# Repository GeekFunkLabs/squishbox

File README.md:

# SquishBox

- [Official Documentation](https://geekfunklabs.github.io/squishbox)
- [Source Repository](https://github.com/GeekFunkLabs/squishbox)

The SquishBox is a compact add-on board and enclosure for Raspberry Pi
(primarily Pi 3B+ and Pi 4) that combines:

- high-quality stereo DAC with 1/4" outputs
- MIDI in/out via TRS minijacks
- 16x2 character LCD
- pushbutton rotary encoder
- breakout GPIO for extra controls, LEDs, and peripherals

This creates a portable embedded platform for audio projects such as synths,
sound modules, pedalboard utilities, sequencers, and music players.

The software package includes ready-to-run applications plus a simple Python API
for building your own.

## Building/Obtaining

This repository includes schematics, PCB fabrication files, BOMs, and enclosure
models for users who want to build their own hardware.

Kits and pre-built units are also available from the Geek Funk Labs
[store](https://geekfunklabs.com/store).

## Installing

The SquishBox software is targeted for a Pi 3B+/4 running Raspberry Pi OS
(64-bit, based on Debian 13 "Trixie") or newer.
Other platforms may work but are not officially tested.

Before installing (even on a fresh system) it's advisable to first run
`sudo apt update && sudo apt upgrade` to update your audio stack.

To run the install script, log in as a regular user and enter:

```bash
bash <(curl -sL geekfunklabs.com/squishbox)
```

Answer the prompts, wait for install to complete,
and reboot the Pi to activate the LCD/button interface.

## Using the SquishBox

On first boot, the SquishBox starts a launcher that lets the user choose
an app to run or modify system settings.
Selections can be made by turning the rotary encoder.
Tapping the rotary encoder confirms a choice.
Pressing and holding the encoder will cancel or return to the previous
screen in most situations.
To safely shut down the SquishBox before disconnecting power,
use the "Shutdown" option in the "Exit" menu.

## Writing SquishBox Apps

The squishbox python package provides access to the LCD,
controls (buttons/encoders), outputs,
and a set of menu-driven interaction helpers.
Here is a simple example app:

```python
import squishbox

sb = squishbox.SquishBox()
card = "hw:sndrpihifiberry"

sb.lcd.clear()
sb.lcd.write("Audio Test", row=0)
while True:
    i, option = sb.menu_choose(["Noise", "Sine", "Exit"], row=1)
    if option == "Noise":
        sb.shell_cmd(f"speaker-test -l2 -c2 -D{card}")
    elif option == "Sine":
        sb.shell_cmd(f"speaker-test -l2 -c2 -tsine -D{card}")
    elif option == "Exit":
        break
```

## Support and Feature Requests

The SquishBox is under active development, and feature requests are
welcome. 

Please post requests/questions to Discussions on GitHub,
and open issues or pull requests for bugs.

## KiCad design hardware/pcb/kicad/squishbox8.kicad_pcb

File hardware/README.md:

# SquishBox Hardware

This directory contains the design and fabrication files for the SquishBox PCB and enclosure. These files are sufficient to fabricate the PCB, source components, and 3D-print a complete enclosure.

Editable design files are also provided to support modification and customization. If anything is missing or unclear, please open a GitHub issue or contact [albedozero@geekfunklabs.com](mailto:albedozero@geekfunklabs.com).

## Directory Structure

```shell
hardware/
  pcb/
    fabrication/    # Gerbers, drill files, pick-and-place, BOM
    kicad/          # KiCad source design files
  enclosure/
    print/          # STL and 3MF files for slicing
    freecad/        # FreeCAD source design files
    step/           # STEP files for other CAD software
```

## PCB Details

The fabrication files include only surface-mount components for automated assembly. Through-hole components are intended to be sourced separately and soldered by hand.

Insert through-hole components from the side matching the silkscreen outlines.

Install the LCD module last, as it blocks access to several solder points.

### P1 Header

Unused pins from the Raspberry Pi GPIO header are broken out to P1 for attaching additional buttons/outputs. Pins 4 and 7 are connected to ground through 1k resistors, to allow connecting LEDs without additional components.

| P1 pin | pad shape | function        |
|--------|-----------|-----------------|
|  1     | diamond   | 5V              |
|  2     | diamond   | 3.3V            |
|  3     | circle    | GPIO4           |
|  4     | notched   | 1k → GND        |
|  5     | circle    | GPIO2 (I2C SDA) |
|  6     | circle    | GPIO3 (I2C SCL) |
|  7     | notched   | 1k → GND        |
|  8     | circle    | GPIO23          |
|  9     | circle    | GPIO24          |
|  10    | circle    | GPIO10          |
|  11    | circle    | GPIO25          |
|  12    | circle    | GPIO9           |
|  13    | circle    | GPIO11          |
|  14    | square    | GND             |

## Case Details

All parts are designed to be printed flat-side down without supports.

* PLA is sufficient, other materials may be used for desired traits
* Infill amount is not critical due to the small interior volume
* Use at least 2–3 wall layers for adequate strength

Three enclosure variants are provided:

* **basic** — Fits Raspberry Pi 3 Model B+ / Raspberry Pi 4 Model B. A Raspberry Pi 5 can fit, but not with the standard fan installed.
* **deluxe** — Fits Pi 3/4 and includes mounting points for two momentary footswitches and two LEDs, which can be connected to the P1 header on the SquishBox PCB.
* **mini** — Fits Raspberry Pi Model A+, with an enlarged cutout to accommodate wide USB cables or adapters.

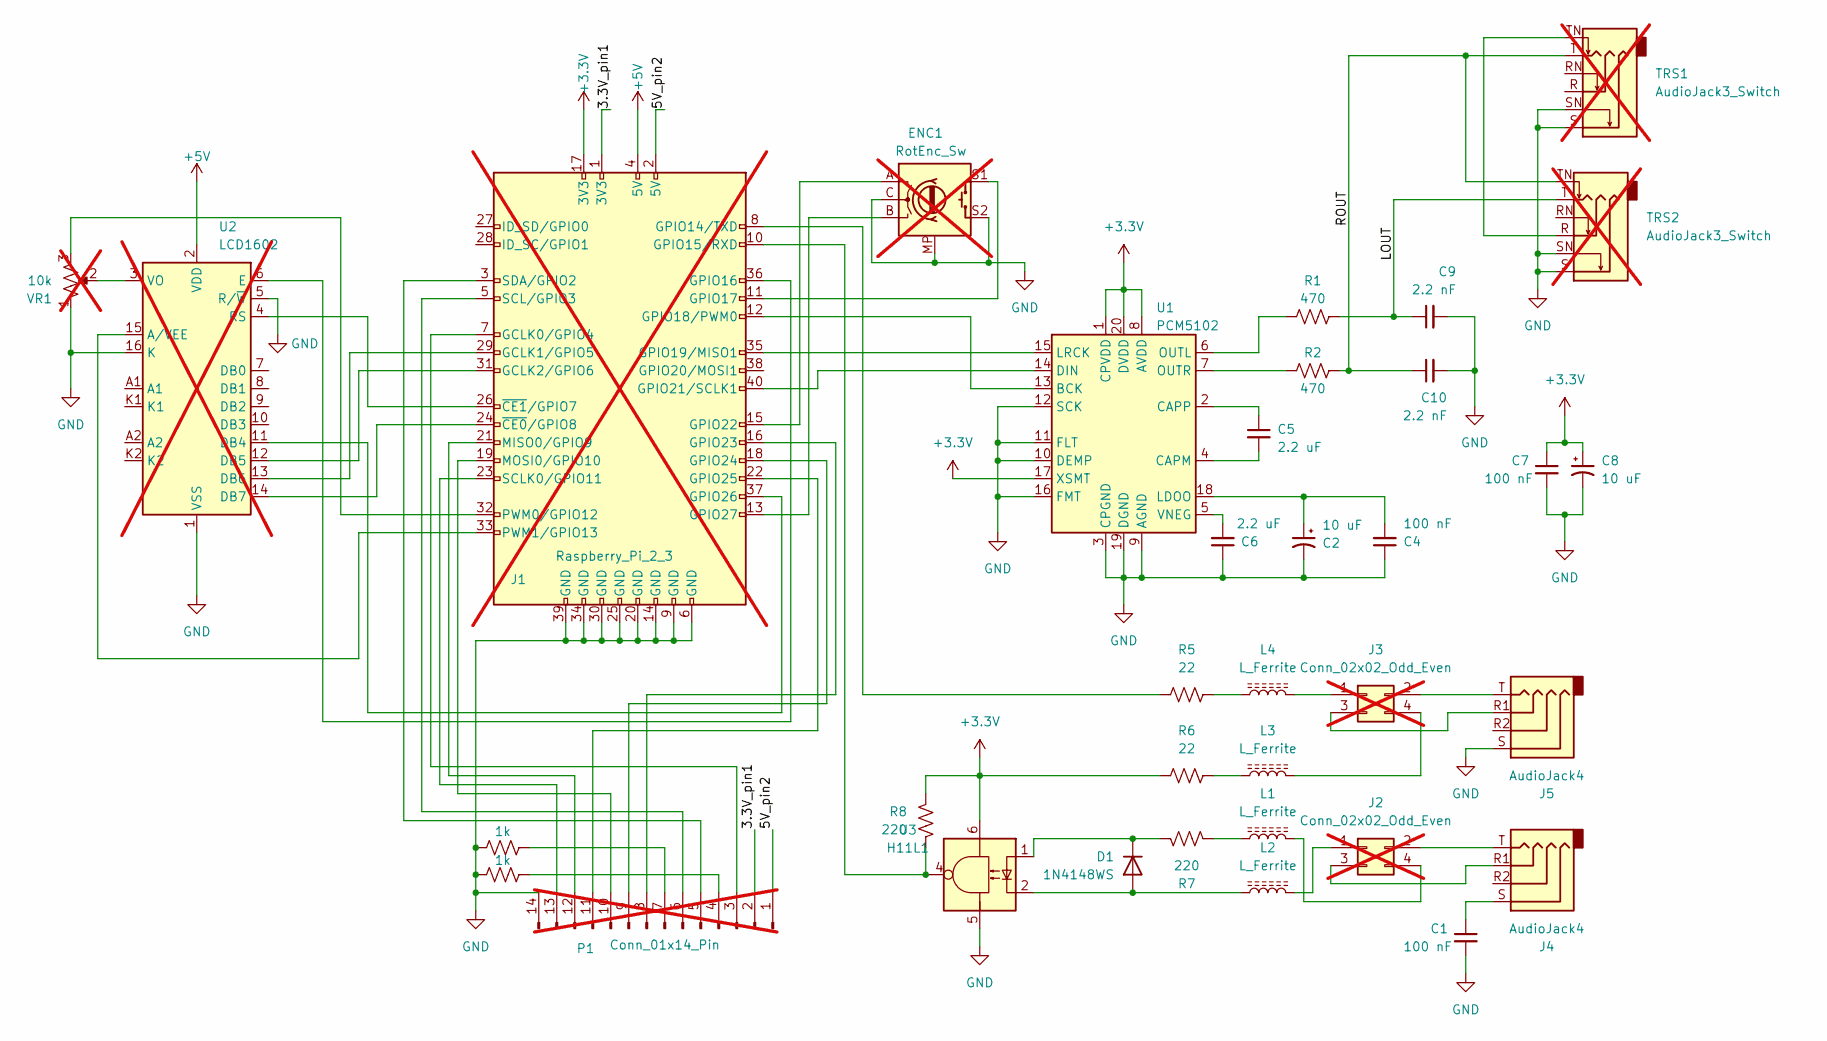
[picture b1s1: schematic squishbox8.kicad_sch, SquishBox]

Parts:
C1, C4, C7: 100 nF; C_0805_2012Metric; MPN 0805F104M500NT; LCSC C28378
C2, C8: 10 uF; C_0805_2012Metric; MPN 0805B106K100NT; LCSC C90544
C5, C6: 2.2 uF; C_0805_2012Metric; MPN 0805B225K250NT; LCSC C74690
C9, C10: 2.2 nF; C_0805_2012Metric; MPN 0805B222K101NT; LCSC C49956
D1: 1N4148WS; D_SOD-323; MPN 1N4148WS; LCSC C2128
ENC1: RotEnc_Sw; RotaryEncoder_Alps_EC11E-Switch_Vertical_H20mm; not fitted
J1: Raspberry_Pi_2_3; PinSocket_2x20_P2.54mm_Vertical; not fitted
J2, J3: Conn_02x02_Odd_Even; PinHeader_2x02_P2.54mm_Vertical; not fitted
J4, J5: AudioJack4; Jack_3.5mm_KoreanHropartsElec_PJ-320D-4A_Horizontal; MPN PJ-320D; LCSC C431535
L1, L2, L3, L4: L_Ferrite; L_0603_1608Metric; MPN GZ1608D601TF; LCSC C1002
P1: Conn_01x14_Pin; PinHeader_1x14_P2.54mm_Vertical; not fitted
R1, R2: 470; R_0805_2012Metric; MPN RS-05K471JT; LCSC C119076
R3, R4: 1k; R_0805_2012Metric; MPN ARG05FTC1001; LCSC C218388
R5, R6: 22; R_2010_5025Metric; MPN FRC2010J220TS; LCSC C3000647
R7, R8: 220; R_1206_3216Metric; MPN 1206W4J0221T5E; LCSC C25363
TRS1, TRS2: AudioJack3_Switch; Jack_6.35mm_Neutrik_NMJ6HFD4_Horizontal; not fitted
U1: PCM5102; TSSOP-20_4.4x6.5mm_P0.65mm; MPN PCM5102APWR; LCSC C107671
U2: LCD1602; PinSocket_1x16_P2.54mm_Vertical; not fitted
U3: H11L1; SMDIP-6_W9.53mm; MPN H11L1S(TA); LCSC C78589
VR1: 10k; Potentiometer_Piher_PT-6-V_Vertical; not fitted

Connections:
+3.3V: C7.1, C8.1, J1.17 (3V3), R6.1, R8.1, U1.1 (CPVDD), U1.8 (AVDD), U1.17 (XSMT), U1.20 (DVDD), U3.6
+5V: J1.4 (5V), U2.2 (VDD)
/3.3V_pin1: J1.1 (3V3), P1.2
/5V_pin2: J1.2 (5V), P1.1
/LOUT: C9.1, R1.2, TRS2.T
/ROUT: C10.1, R2.2, TRS1.T, TRS2.TN
GND: C1.2, C2.2, C4.1, C6.1, C7.2, C8.2, C9.2, C10.2, ENC1.C, ENC1.MP, ENC1.S2, J1.6 (GND), J1.9 (GND), J1.14 (GND), J1.20 (GND), J1.25 (GND), J1.30 (GND), J1.34 (GND), J1.39 (GND), J5.S, P1.14, R3.2, R4.2, TRS1.S, TRS1.SN, TRS2.S, TRS2.SN, U1.3 (CPGND), U1.9 (AGND), U1.10 (DEMP), U1.11 (FLT), U1.12 (SCK), U1.16 (FMT), U1.19 (DGND), U2.1 (VSS), U2.5 (R/~W), U2.16 (K), U3.5, VR1.1
unnamed: C1.1, J4.S
unnamed: D1.2 (A), L2.1, U3.2
unnamed: D1.1 (K), R7.1, U3.1
unnamed: J1.7 (GCLK0/GPIO4), P1.3
unnamed: J1.29 (GCLK1/GPIO5), U2.13 (DB6)
unnamed: J1.31 (GCLK2/GPIO6), U2.12 (DB5)
unnamed: J1.8 (GPIO14/TXD), R5.1
unnamed: J1.10 (GPIO15/RXD), R8.2, U3.4
unnamed: J1.36 (GPIO16), U2.6 (E)
unnamed: ENC1.S1, J1.11 (GPIO17)
unnamed: J1.12 (GPIO18/PWM0), U1.13 (BCK)
unnamed: J1.35 (GPIO19/MISO1), U1.15 (LRCK)
unnamed: J1.40 (GPIO21/SCLK1), U1.14 (DIN)
unnamed: ENC1.A, J1.15 (GPIO22)
unnamed: J1.16 (GPIO23), P1.8
unnamed: J1.18 (GPIO24), P1.9
unnamed: J1.22 (GPIO25), P1.11
unnamed: J1.37 (GPIO26), U2.11 (DB4)
unnamed: ENC1.B, J1.13 (GPIO27)
unnamed: J1.21 (MISO0/GPIO9), P1.12
unnamed: J1.19 (MOSI0/GPIO10), P1.10
unnamed: J1.32 (PWM0/GPIO12), VR1.3
unnamed: J1.33 (PWM1/GPIO13), U2.15 (A/VEE)
unnamed: J1.23 (SCLK0/GPIO11), P1.13
unnamed: J1.5 (SCL/GPIO3), P1.6
unnamed: J1.3 (SDA/GPIO2), P1.5
unnamed: J1.24 (~CE0/GPIO8), U2.14 (DB7)
unnamed: J1.26 (~CE1/GPIO7), U2.4 (RS)
unnamed: J2.1, L2.2
unnamed: J2.2, J4.T
unnamed: J2.3, J4.R1
unnamed: J2.4, L1.2
unnamed: J3.1, L4.2
unnamed: J3.2, J5.T
unnamed: J3.3, J5.R1
unnamed: J3.4, L3.2
unnamed: L1.1, R7.2
unnamed: L3.1, R6.2
unnamed: L4.1, R5.2
unnamed: P1.4, R3.1
unnamed: P1.7, R4.1
unnamed: TRS1.TN, TRS2.R
unnamed: C5.2, U1.4 (CAPM)
unnamed: C5.1, U1.2 (CAPP)
unnamed: C2.1, C4.2, U1.18 (LDOO)
unnamed: R1.1, U1.6 (OUTL)
unnamed: R2.1, U1.7 (OUTR)
unnamed: C6.2, U1.5 (VNEG)
unnamed: U2.3 (VO), VR1.2

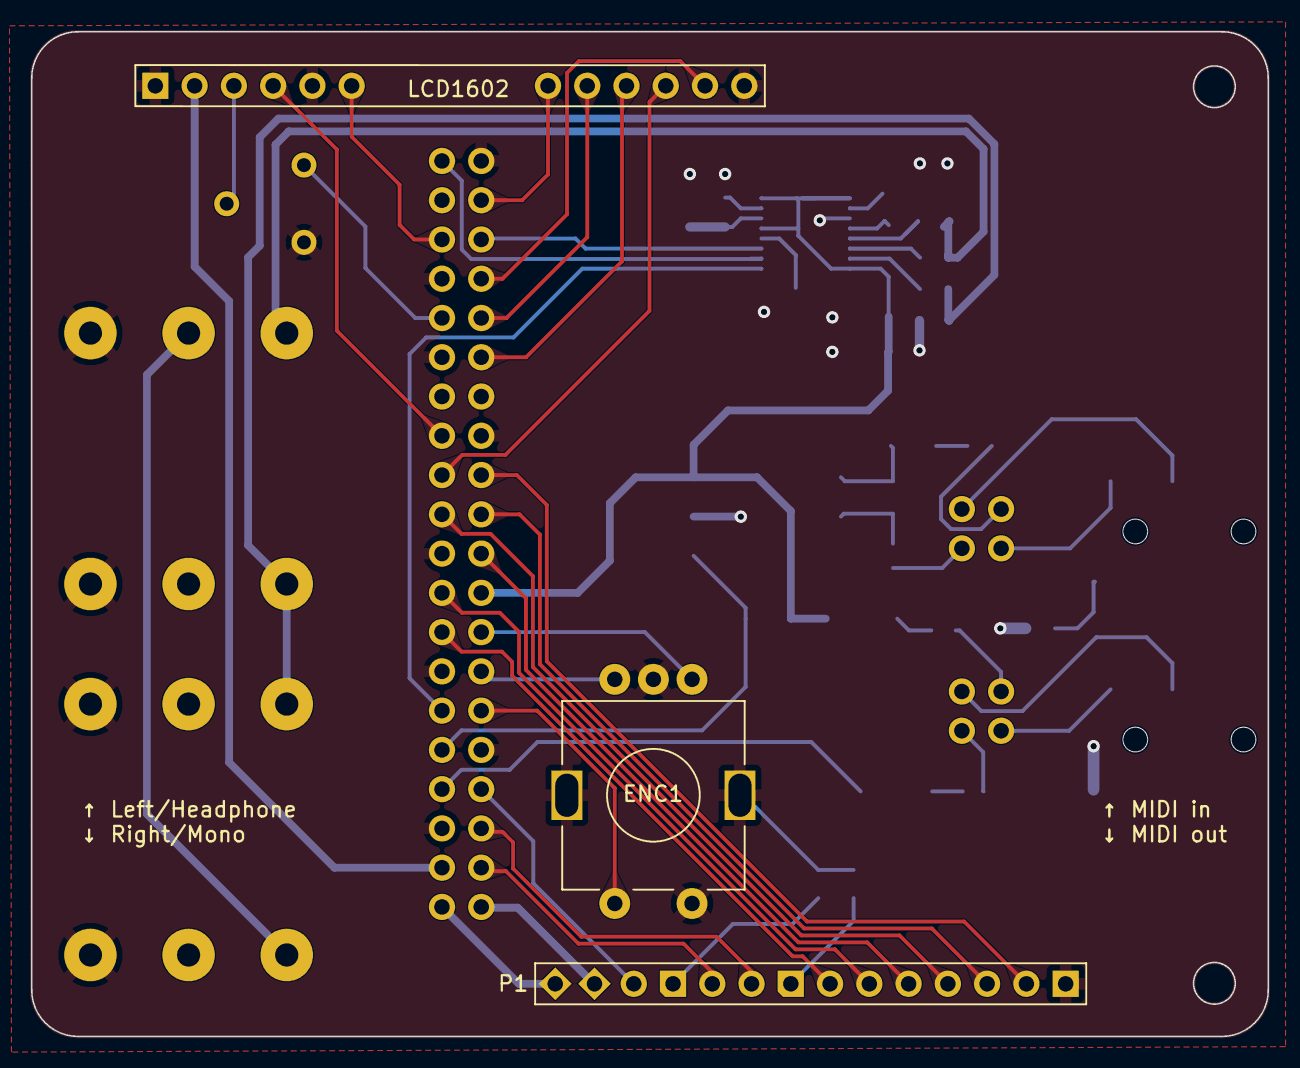
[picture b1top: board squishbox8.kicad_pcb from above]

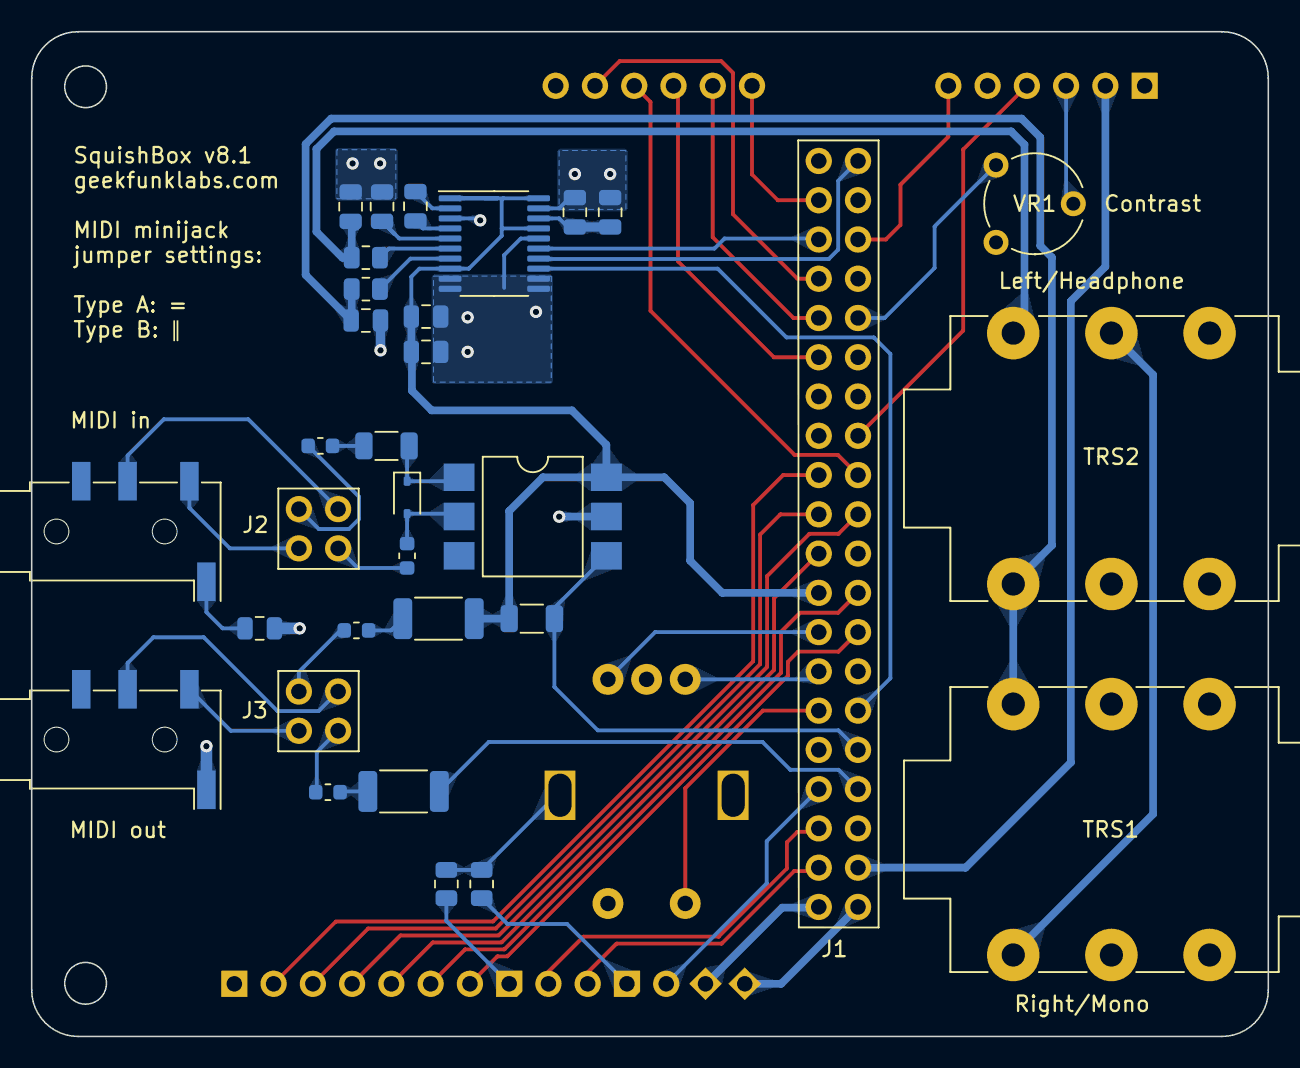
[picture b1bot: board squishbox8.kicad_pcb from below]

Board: 2 copper layers, 80.0 x 65.0 mm, 35 parts (32 on the bottom side), 56 nets.

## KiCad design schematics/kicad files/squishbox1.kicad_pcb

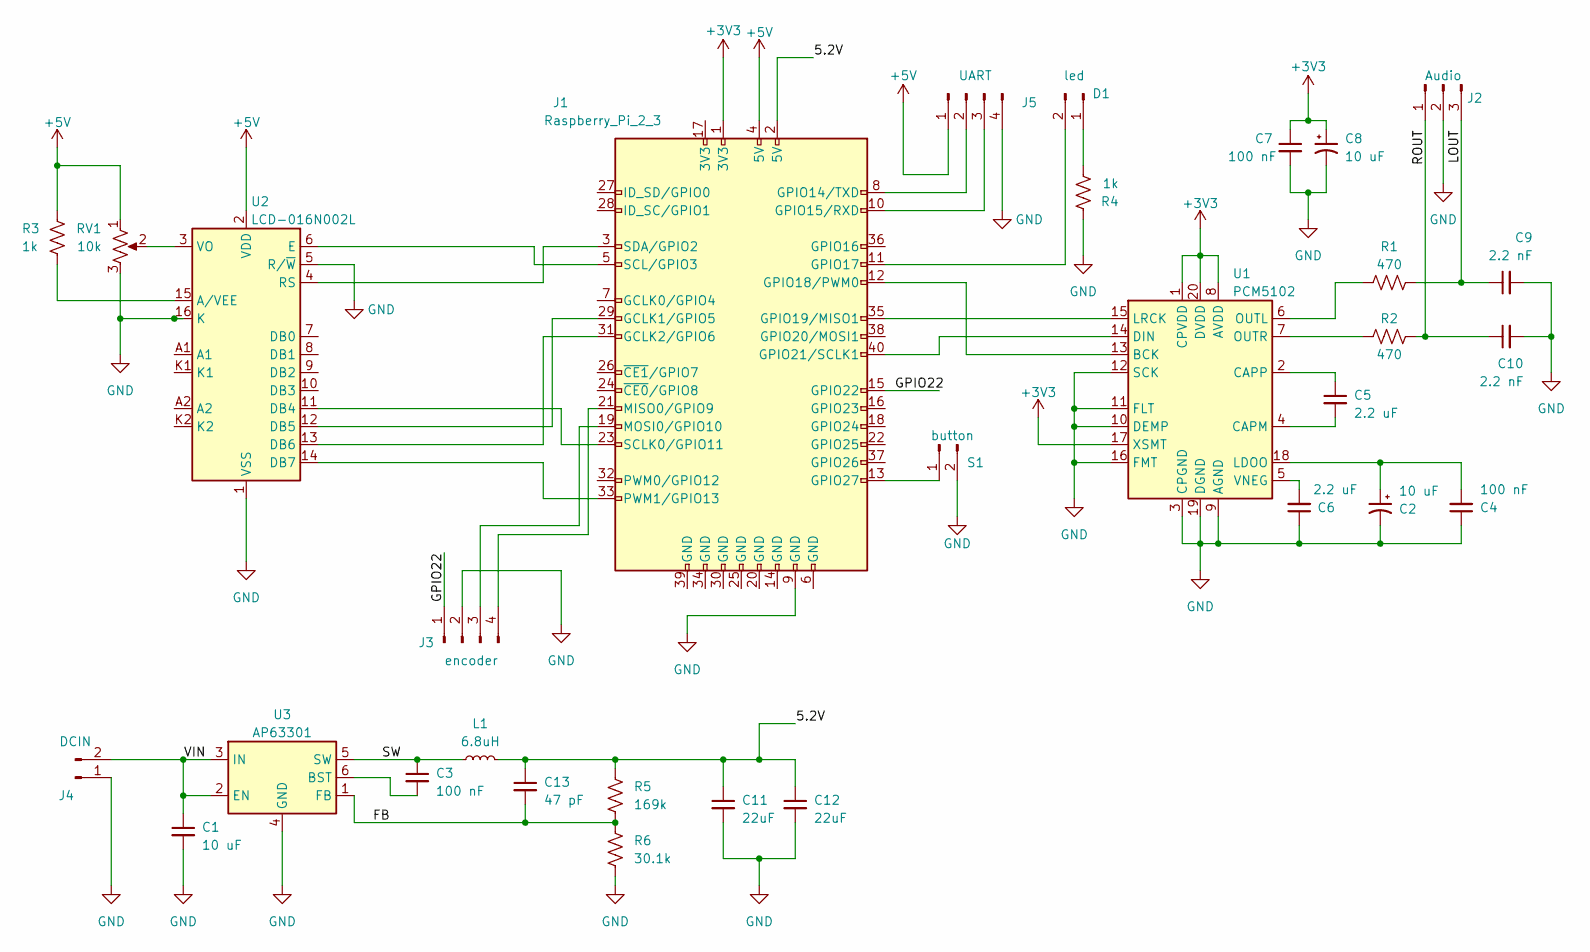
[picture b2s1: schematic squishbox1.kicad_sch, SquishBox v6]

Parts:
C1, C2, C8: 10 uF; C_0805_2012Metric
C3, C4, C7: 100 nF; C_0805_2012Metric
C5, C6: 2.2 uF; C_0805_2012Metric
C9, C10: 2.2 nF; C_0805_2012Metric
C11, C12: 22uF; C_0805_2012Metric
C13: 47 pF; C_0805_2012Metric
D1: led; PinHeader_1x02_P2.54mm_Vertical
J1: Raspberry_Pi_2_3; PinSocket_2x20_P2.54mm_Vertical
J2: Audio; PinHeader_1x03_P2.54mm_Vertical_centerground
J3: encoder; PinHeader_1x04_P2.54mm_Vertical_unpol
J4: DCIN; PinHeader_1x02_P2.54mm_Vertical
J5: UART; PinHeader_1x04_P2.54mm_Vertical
L1: 6.8uH; L_Changjiang_FNR5030S
R1, R2: 470; R_0805_2012Metric
R3, R4: 1k; R_0805_2012Metric
R5: 169k; R_0805_2012Metric
R6: 30.1k; R_0805_2012Metric
RV1: 10k; Potentiometer_ACP_CA6-H2,5_Horizontal
S1: button; PinHeader_1x02_P2.54mm_Vertical_unpol
U1: PCM5102; TSSOP-20_4.4x6.5mm_P0.65mm
U2: LCD-016N002L; PinSocket_1x16_P2.54mm_Vertical
U3: AP63301; TSOT-23-6

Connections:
+3V3: C7.1, C8.1, J1.1 (3V3), U1.1 (CPVDD), U1.8 (AVDD), U1.17 (XSMT), U1.20 (DVDD)
+5V: J1.4 (5V), J5.1, R3.1, RV1.1, U2.2 (VDD)
/5.2V: C11.1, C12.1, C13.1, J1.2 (5V), L1.2, R5.1
/FB: C13.2, R5.2, R6.1, U3.1 (FB)
/GPIO22: J1.15 (GPIO22), J3.1
/LOUT: C9.1, J2.3, R1.2
/ROUT: C10.1, J2.1, R2.2
/SW: C3.1, L1.1, U3.5 (SW)
/VIN: C1.1, J4.2, U3.2 (EN), U3.3 (IN)
GND: C1.2, C2.2, C4.1, C6.1, C7.2, C8.2, C9.2, C10.2, C11.2, C12.2, J1.9 (GND), J2.2, J3.2, J4.1, J5.4, R4.1, R6.2, RV1.3, S1.2, U1.3 (CPGND), U1.9 (AGND), U1.10 (DEMP), U1.11 (FLT), U1.12 (SCK), U1.16 (FMT), U1.19 (DGND), U2.1 (VSS), U2.5 (R/~W), U2.16 (K), U3.4 (GND)
unnamed: D1.1, R4.2
unnamed: D1.2, J1.11 (GPIO17)
unnamed: J1.29 (GCLK1/GPIO5), U2.12 (DB5)
unnamed: J1.31 (GCLK2/GPIO6), U2.13 (DB6)
unnamed: J1.8 (GPIO14/TXD), J5.2
unnamed: J1.10 (GPIO15/RXD), J5.3
unnamed: J1.12 (GPIO18/PWM0), U1.13 (BCK)
unnamed: J1.35 (GPIO19/MISO1), U1.15 (LRCK)
unnamed: J1.40 (GPIO21/SCLK1), U1.14 (DIN)
unnamed: J1.13 (GPIO27), S1.1
unnamed: J1.21 (MISO0/GPIO9), J3.4
unnamed: J1.19 (MOSI0/GPIO10), J3.3
unnamed: J1.33 (PWM1/GPIO13), U2.14 (DB7)
unnamed: J1.23 (SCLK0/GPIO11), U2.11 (DB4)
unnamed: J1.5 (SCL/GPIO3), U2.6 (E)
unnamed: J1.3 (SDA/GPIO2), U2.4 (RS)
unnamed: C5.2, U1.4 (CAPM)
unnamed: C5.1, U1.2 (CAPP)
unnamed: C2.1, C4.2, U1.18 (LDOO)
unnamed: R1.1, U1.6 (OUTL)
unnamed: R2.1, U1.7 (OUTR)
unnamed: C6.2, U1.5 (VNEG)
unnamed: R3.2, U2.15 (A/VEE)
unnamed: RV1.2, U2.3 (VO)
unnamed: C3.2, U3.6 (BST)

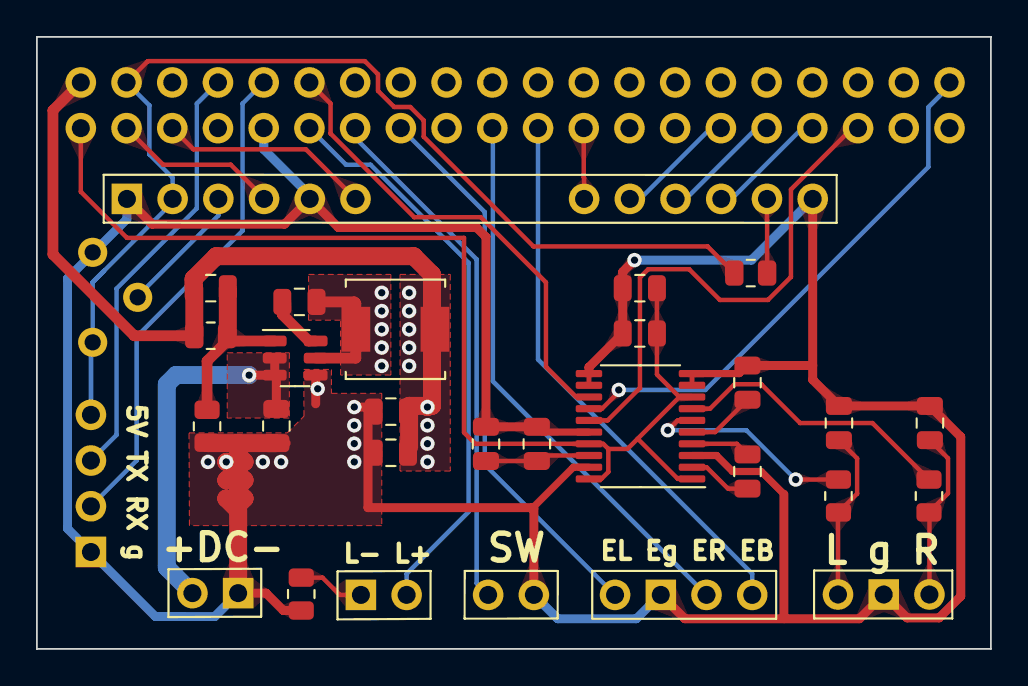
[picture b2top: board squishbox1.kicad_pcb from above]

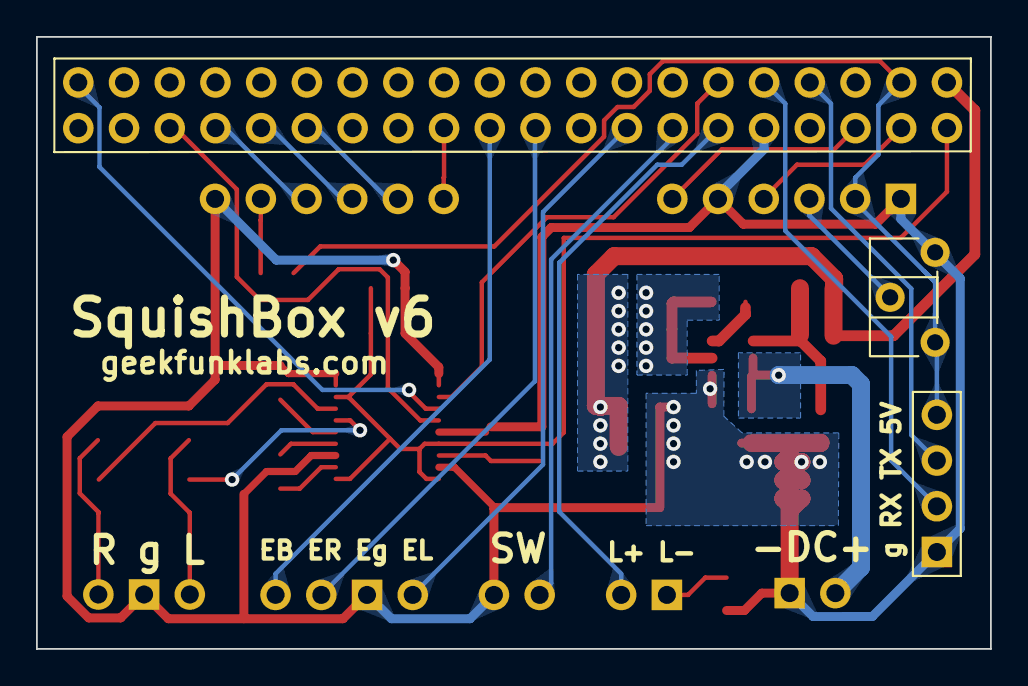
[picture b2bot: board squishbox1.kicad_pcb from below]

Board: 2 copper layers, 53.0 x 34.0 mm, 31 parts (3 on the bottom side), 35 nets.

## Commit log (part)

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2023-12-18 update wifi_settings()
    timeout menu if wifi disabled
2023-12-21 tweaks for standalone fluidpatcher
2023-12-26 config created by squishbox-install
2023-12-26 add bare pi functionality
2023-12-26 update install for standaone fluidpatcher
2023-12-27 adjust file locations for install
2024-01-04 remove midi bank advance
2024-01-14 update docs
2024-01-14 remove example-sphinx.yml
2024-01-14 rename build.yaml
2024-01-14 deploy: 5b198c94e2ff3404532cad78a0698799387be3d8
2024-04-02 typo bankinc -> selpatch
2024-04-14 working on fix for gpiochip interface
2024-04-23 deploy: 63c9bc7983403341f0f1794ed609a22ee9fa651a
2024-04-23 deploy: 1c7e73702ba00d4b66192df6f27b81ae37cc7a4e
2024-04-24 add autodocumentation
2024-04-24 deploy: d6178c9d33c1667514de89b584945f9777ede0bf
2024-04-25 check for python3-rpi-lgpio package
    newer kernels with the gpiochip device need the python3-rpi-lgpio package to properly set edge detection. Checking for existence of this package seems the best way to determine whether it's needed
2024-04-25 deploy: 784a53d0211ae9e67f1317860908b842f50fda2f
2024-05-03 deploy: 9e4f266747718c5712cd5dc32b1367f5313b5ae5
2024-05-19 allow priority scheduling and memlocking
2024-05-19 deploy: 8ff6f3bceee238f0e8f88ab8e8d3d8930315eda1
2024-05-19 adjust permissions for web file manager
2024-05-19 deploy: a73e25920bd807d8a4a7af55fa03befc69b36f39
2024-05-22 fix syntax error
2024-05-22 deploy: 6f2329241a4eea98686859a81db9248e620df070
2024-06-19 fix installdir and lgpio logic
2024-06-19 deploy: 320a21fec42c841f47c6e2efcd64c7f7254cad8a
2024-06-27 adjust for API changes
2024-06-27 deploy: f965edf74c9586e2f250ae9f8f6363b6d7b4c697
2024-06-28 fixes bug where was receiving all audiocard name strings in index 0 instead of having them populate successive indexes
2024-06-29 deploy: 410a8fe07ae3611b6d22c197434bf9f069066e84
2025-08-13 initial rework for v0.9
    - update for use with libgpiod
    - clean up API
    - remove user need to poll, update LCD
    - add dynamic binding for buttons, controls
2025-08-18 Add module-level squishbox_instance constant to simulate singleton
2025-09-01 add fluidbox.py
2025-09-15 add encoder debouncing
2025-09-15 skip PWM for level=0,100
2025-09-15 make SquishBox singleton
2025-10-20 reorganize for packaging
2025-10-23 add fluidbox to scripts
2025-10-23 adjust class checking in fluidbox
2025-10-27 fix backlight/contrast state save
2025-10-27 clean up edit_sounds
2025-10-27 fix imports
2025-10-29 remove extra file
2025-10-30 fix glyph access
2025-10-31 expose set_cursormode and set_cursorpos
2025-10-31 fix typos and string conversions
2025-10-31 tweak ui behavior
2025-11-02 clarify edit_layers()
2025-11-03 update fluidbox
2025-11-06 add midi connection menu
2025-11-07 add startup_script persistence to launcher
2025-11-08 create sbedit script
2025-11-08 modify menu_entertext to accept empty strings
2025-11-12 add glyphs to config file
2025-11-12 add sbedit and glyphedit
2025-11-12 adjust menu behavior
2025-11-12 allow midi connect to/from "any"
2025-11-25 add amsynthbox script
2025-11-28 rename progresswheel to activitywheel
2025-11-28 clarify src/dest names
2025-11-30 update amsynthbox
2025-12-01 add djbox
2025-12-01 fix amsynth parameter calculation
2025-12-19 add trackbox
2025-12-19 add trackbox script
2025-12-22 create script exception fallback
2025-12-26 remove folder icon
2025-12-26 update sbedit
2025-12-26 update trackbox
2025-12-26 add sbcommander and keyboard input
2025-12-27 fix glyph redefinition bug
2025-12-27 add dismiss() for clean GStreamer exit
2025-12-30 update squishbox
2026-02-09 move scripts to apps
2026-02-17 replace activity_* with contextmanager
2026-02-17 refactor fpatcherbox with FPBox class
2026-03-03 Add fluidpatcher as git submodule
2026-03-03 remove gfl_logo.png
2026-03-05 point installer to legacy fluidpatcher commit
2026-03-06 add files for debian packaging
2026-03-06 use activity() context manager in menu_wifisettings
2026-03-06 comment out midi_connect()
2026-03-11 fix raw strings in regex
2026-03-11 packaging tweaks
2026-03-11 removed fluidpatcher as submodule
2026-03-16 reorganize workflows
2026-03-16 update packaging dependencies
2026-03-20 modify config system
2026-03-26 no need to set SQUISHBOX_CONFIG
2026-03-26 update docstrings
2026-03-26 fix file modes
2026-03-27 add squishbox-web package
2026-03-27 update installer script
2026-03-28 fix changelog
2026-03-28 fix package building bugs
2026-03-29 change workflow container
2026-03-29 change runs-on to debian:trixie
2026-03-29 Update build dependencies in workflow
    Remove architecture specification from build dependencies.
2026-03-30 Update build dependencies in workflow
    Added gcc and libasound2-dev to build dependencies.
2026-03-30 set build dependency arch for libasound2-dev to native
2026-03-30 set gcc and pkg-config to native build
2026-03-30 Make debian/rules executable
2026-03-30 add cross flag to dpkg-buildpackage
2026-03-30 correct name of package pkgconf
2026-03-30 fix hardware overlays location
2026-03-30 install libc6 and libasound2 for dependency resolution
2026-03-30 modify libasound2 to libasound2t64
2026-03-30 override compiler
2026-03-30 Test CI build
2026-03-30 set cross build profile in dpkg-buildpackage
2026-03-30 clean build artifacts before each build
2026-03-30 install libasound2-dev for cross-build
2026-03-30 use curl to download soundfonts
2026-03-30 gate branch push
2026-03-30 call make explicitly
2026-04-03 fix file locations
2026-04-03 fix regression in squishbox-system.install
2026-04-03 tweak packaging
2026-04-04 remove usb mount service
2026-04-04 correct install directories
2026-04-08 catch missing cfg file in load_config
2026-04-08 fix regression in trackbox.py
2026-04-09 rename ibom.html to squishbox8_ibom.html
2026-04-09 Document P1 header pin functions in README
    Added details about the P1 header and its pin functions.
2026-04-09 add pad shape descriptions to README.md
2026-04-09 add readme for squishbox apps
2026-04-09 update apps readme
2026-04-30 add data/__init__.py
2026-04-30 big doc update
2026-04-30 project tweaks
2026-04-30 remove unneeded doc files
2026-05-01 deploy: 811d109ca75e709f342f1acab4273d7dac690fea
2026-05-01 add python publish workflow
2026-05-01 deploy: 4a8a73efe6d961aa030cca2e8f88c553540ca1fa
2026-05-03 make example code more compact
2026-05-03 update install script
2026-05-03 deploy: 2548da5e49c5e436d049768dcc1628e41ec1bba1
2026-05-03 simplify installer path
2026-05-03 bump version
2026-05-03 fix working directory
2026-05-03 deploy: d1957813608325029dc0d555b9e3380056226983
2026-05-03 fix arm64 building
2026-05-03 add proper cross building libs
2026-05-03 deploy: 4efd9f8a867d47bb3365e041ccca008836436807
2026-05-03 deploy: 5fca8ac9b4fe33fd4a36d3ab53950cd2995104b3
2026-05-03 correct package location for release upload
2026-05-03 deploy: d9f6a9545cb224cc38c171f5bff7bd3dfc66d17b
2026-05-03 deploy: ed258b950156cd543d70eef993aeaba8910b9a1a
2026-05-04 fix: address incorrect paths
2026-05-04 fix: change module hierarchy reference
2026-05-04 move venv to user directory
2026-05-04 deploy: dc91506465c74354d629e4ff0ea907c1682ebf00
2026-05-04 deploy: ce55baa9f03a90de47708fbc6c97c88b05d5d104
2026-05-04 properly organize packaging layout
2026-05-04 test packaging
2026-05-04 deploy: 859815a65bc5785f7bffed1c646d0ffa799b714d
2026-05-04 remove squishbox-system.conffiles
2026-05-04 deploy: b34194facf12dd18470fbc908580b49277deab18
2026-05-04 test package building on push
2026-05-04 adjust installer script command
2026-05-04 deploy: 285834e298861253d4b427dc68568839326381c4
2026-05-04 fix web install
2026-05-04 deploy: a5f17ef4b26ef949b23116f18730cd4290276551
2026-05-04 keep current files when unpacking soundfonts
2026-05-04 un-ignore service files in package
2026-05-04 deploy: 70871e3a880ef3d283ec4b9b008ed8a4ade2d06f
2026-05-04 deploy: 79ca491c5ae0890f53e306577a0d9b80431a56b3
2026-05-04 move venv to .local/share/squishbox/venv
2026-05-04 deploy: bdd6f362681274f38cac3638eb69085c5257068a
2026-05-04 copy packages in workflow
2026-05-04 reorganize package directory
2026-05-04 add config files to package`
2026-05-04 deploy: 391ca31b331a91b301a9ce7d325f8f5511ef2228
2026-05-04 fix squishbox-system.install file locations
2026-05-04 deploy: 6435fdda15e45151d81ecdaa1f7181698474582e
2026-05-05 skip old files when downloading soundfonts
2026-05-05 deploy: 9f857398a431f8cdcc4cc95e4f0497eac70fefb6
2026-05-05 fix install script
2026-05-05 deploy: ff98e8a180e59741dc9bec09df2af0b7449d6957
2026-05-05 deploy: f1198ae54fceefb839659c62d1be4479ad8a3229
2026-05-05 change soundfont locations
2026-05-05 create soundfonts directory
2026-05-05 deploy: f5c82bbacfd1781a15968b71bf4142d2ebcded22
2026-05-06 copy default configs if needed
2026-05-06 deploy: 97df1e66f3ce8c5c289680f168ee1d812a088ae8
2026-05-06 use apache instead of nginx for squishbox-web
2026-05-06 deploy: d25f7147158e1bd0a90cacabc10139cbba3260e9
2026-05-06 deploy: d034a8cb925199052dd71111e7a1faa6d6eab351
2026-05-06 deploy: b221ca61e8b3786203a6e26ec617174c067d8480
2026-05-06 fix regression in install script
2026-05-06 deploy: eb751f5da9dbb60732e12fa0a3646611727f0a6a
2026-05-07 catch errors loading banks/checking wifi
2026-05-07 deploy: 61d58b2dc8a4fd6b905259806c6273d567e4f7c2
2026-05-07 depend squishbox-full package on libfluidsynth3 instead of fluidsynth fluidsynth downloads unnecessary extra files and installs unwanted services
2026-05-07 deploy: 69e11e6049876cdba528be6f52af6ad78a894e6b
2026-05-15 add midi.send_message()
2026-05-15 bind hardware events to midi messages
2026-05-15 add toggling "on"/"off" events for buttons
2026-05-15 add passthrough, on_change arguments to menu_choose
2026-05-17 change some names
2026-05-17 fix regression in get_action()
2026-05-17 convert setcursormode, setcursorpos to attributes
2026-05-18 deploy: f408e7a588f59ee83e324928f5e41c25d6a4feb8
2026-05-18 clean up event loop
2026-05-18 fix regression in cursor property access
2026-05-18 add pyyaml to autodoc_mock_imports
2026-05-18 deploy: 33d7094582570d2520c351c02733c193a5bf3ccb
2026-05-18 fix autodoc_mock_imports
2026-05-18 deploy: 42bf9da6b6768166c14f6c230e4b7392c4b0f9cc
2026-05-19 remove unneeded contrast_level and backlight_level properties
2026-05-19 deploy: 8ca8ba8c366c8e7c12a3cb444d3190e7dcc0f75c
2026-05-19 fix indentation issue
2026-05-19 deploy: efd1ab3a434e09154e08f92157f5239bcc4aa2ad
2026-05-19 fix dependencies for docs
2026-05-19 deploy: 4ec8875e279fd0ba312cbed14c37a5563ab6d079
2026-05-19 fix venv location in system unit template
2026-05-19 deploy: 46d922ba91b4f0b75418e82c9c3f72ab13d98c45
2026-05-27 resolve yaml/button toggle syntax collision
2026-05-27 fix typing in ControlChangeEvent creation
2026-05-27 deploy: 2f20d934e253650c4b08aec6b82478efe8d7f6a1
2026-05-28 deploy: 0367f8afa4795a8df5f4c088b2d957cd4423e2a5
2026-06-03 update factory content installation
2026-06-03 deploy: cd9288d20756e86b770d0eda7ca6e410341bfaae
2026-06-03 adjust fpatcherbox custom rule parameter behavior
2026-06-03 deploy: b8c6ad11a70db6b796e8fa567f4315365bc80d21
2026-06-03 deploy: ad300739e8e9d45cfd737d6719e54656807573be
2026-06-11 ignore no_export ports
2026-06-11 actually allow any>any connections
2026-06-11 clean up configs
2026-06-11 remove python gi dependency
2026-06-11 separate install tasks more sensibly
2026-06-11 wait for NetworkManager to start service
2026-06-11 add SquishBox.close() method
2026-06-11 call apps as subprocesses instead of importing
2026-06-11 remove singleton-like characteristics
2026-06-11 properly redirect ports
2026-06-11 clarify LED installation
2026-06-11 deploy: fd1634456ce966d1dae1960ef04fee212e252290
2026-06-12 fix garbled commit
2026-06-13 add FPBox().pname default value
2026-06-13 allow specifying track end position
2026-06-13 deploy: edbd18acb8d2e6544467a1b3d2781b1b343617a5
2026-06-13 deploy: f849a24f9b7a4cb67517a00bebb997fa3498f166
2026-06-14 fix regression in dpkg install step
2026-06-14 deploy: 9e6c5ea1753dea004ec418e84827874a0a5006f1
2026-06-16 ignore midi through and no self connections
2026-06-16 add nopasswd rule for reboot, power off
2026-06-16 fix example
2026-06-16 deploy: 7ecb512463031310c01ae456e5f4449e9f11f631
2026-06-17 remove index.html during web install
